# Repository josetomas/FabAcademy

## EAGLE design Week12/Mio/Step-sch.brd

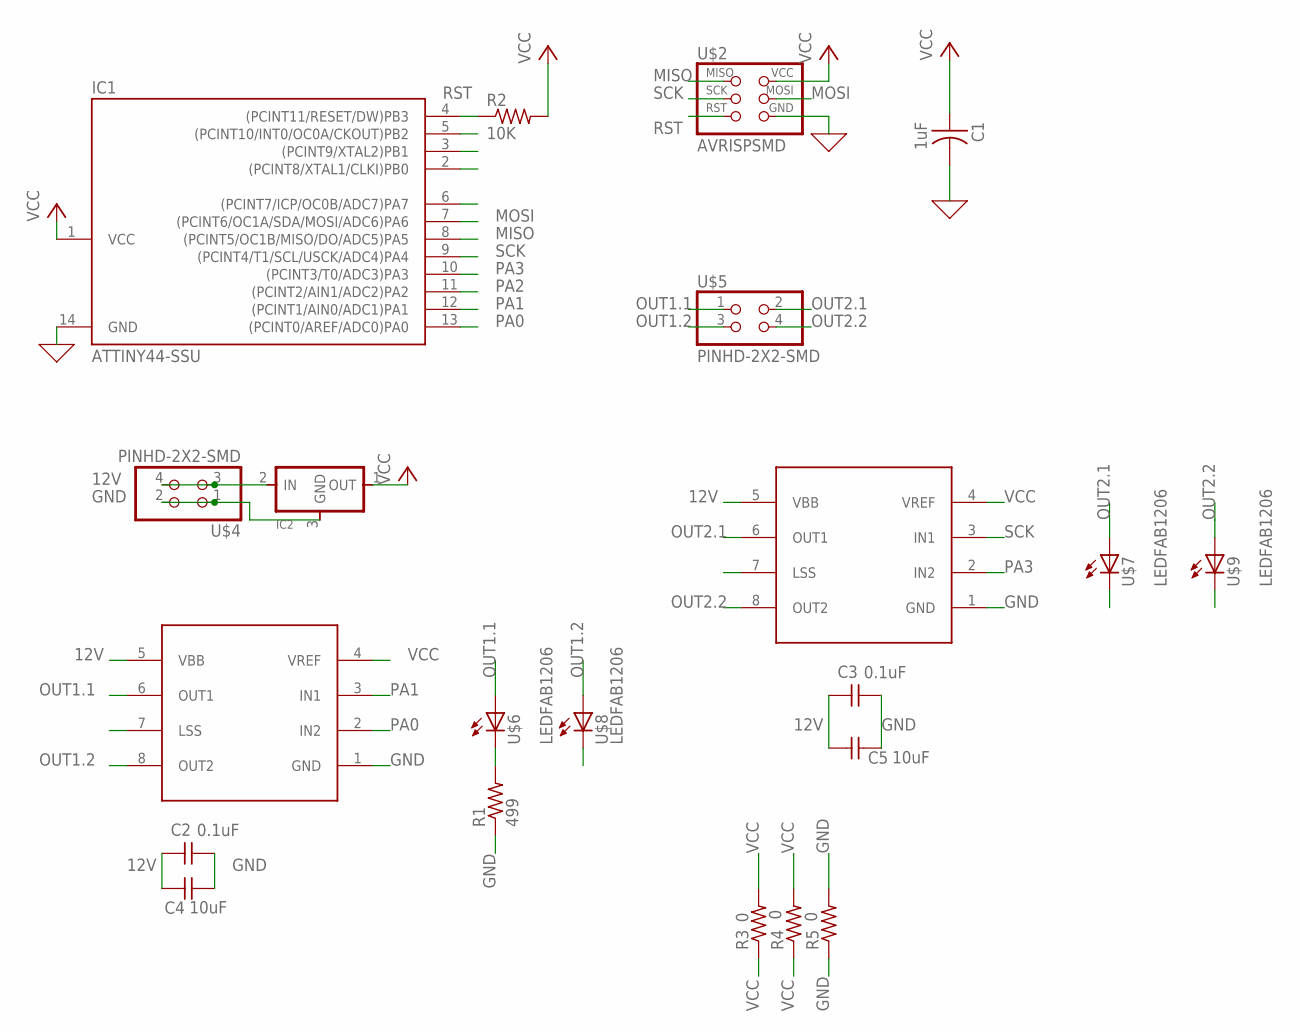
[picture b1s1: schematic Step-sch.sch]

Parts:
C1: 1uF; C1206FAB
C2, C3: 0.1uF; C1206FAB
C4, C5: 10uF; C1206FAB
IC1: ATTINY44-SSU; SOIC14
IC2: REGULATORSOT23; SOT23
R1: 499; R1206FAB
R2: 10K; R1206FAB
R3, R4, R5: 0; R1206FAB
U$1, U$3: A4953-H-BRIDGE-MOTOR-DRIVER; SOIC8
U$2: AVRISPSMD; 2X03SMD
U$4, U$5: PINHD-2X2-SMD; 2X02SMD
U$6, U$7, U$8, U$9: LEDFAB1206; LED1206FAB

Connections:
12V: C2.1, C3.1, C4.1, C5.1, IC2.2 (IN), U$1.5 (VBB), U$3.5 (VBB), U$4.3, U$4.4
GND: C1.2, C2.2, C3.2, C4.2, C5.2, IC1.14 (GND), IC2.3 (GND), R1.1, R5.1, R5.2, U$1.1 (GND), U$2.6 (GND), U$3.1 (GND), U$4.1, U$4.2
MISO: IC1.6 ((PCINT7/ICP/OC0B/ADC7)PA7), IC1.8 ((PCINT5/OC1B/MISO/DO/ADC5)PA5), U$2.1 (MISO)
MOSI: IC1.7 ((PCINT6/OC1A/SDA/MOSI/ADC6)PA6), U$2.4 (MOSI)
OUT1.1: U$1.6 (OUT1), U$5.1, U$6.1 (A)
OUT1.2: U$1.8 (OUT2), U$5.3, U$8.1 (A)
OUT2.1: U$3.6 (OUT1), U$5.2, U$7.1 (A)
OUT2.2: U$3.8 (OUT2), U$5.4, U$9.1 (A)
PA0: IC1.13 ((PCINT0/AREF/ADC0)PA0), U$1.2 (IN2)
PA1: IC1.12 ((PCINT1/AIN0/ADC1)PA1), U$1.3 (IN1)
PA2: IC1.11 ((PCINT2/AIN1/ADC2)PA2)
PA3: IC1.10 ((PCINT3/T0/ADC3)PA3), U$3.2 (IN2)
RES: R1.2, U$6.2 (C), U$7.2 (C), U$8.2 (C), U$9.2 (C)
RST: IC1.4 ((PCINT11/RESET/DW)PB3), R2.1, U$2.5 (RST)
SCK: IC1.9 ((PCINT4/T1/SCL/USCK/ADC4)PA4), U$2.3 (SCK), U$3.3 (IN1)
VCC: C1.1, IC1.1 (VCC), IC2.1 (OUT), R2.2, R3.1, R3.2, R4.1, R4.2, U$1.4 (VREF), U$2.2 (VCC), U$3.4 (VREF)

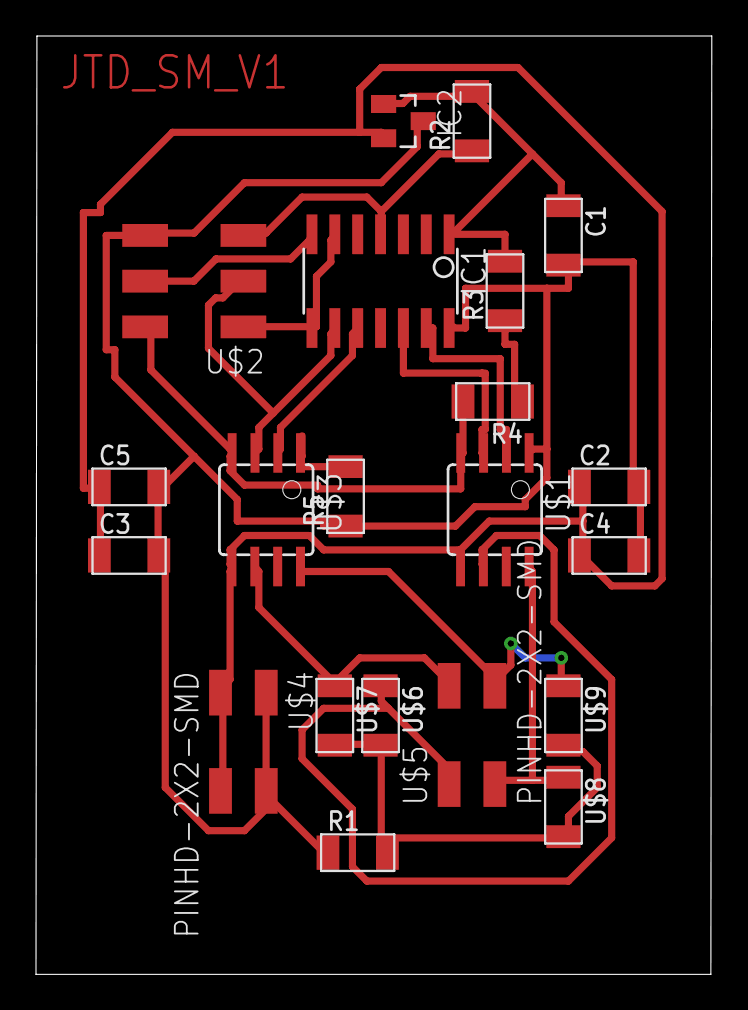
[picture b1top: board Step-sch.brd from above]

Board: 2 copper layers, 37.5 x 52.1 mm, 21 parts (0 on the bottom side), 15 nets.

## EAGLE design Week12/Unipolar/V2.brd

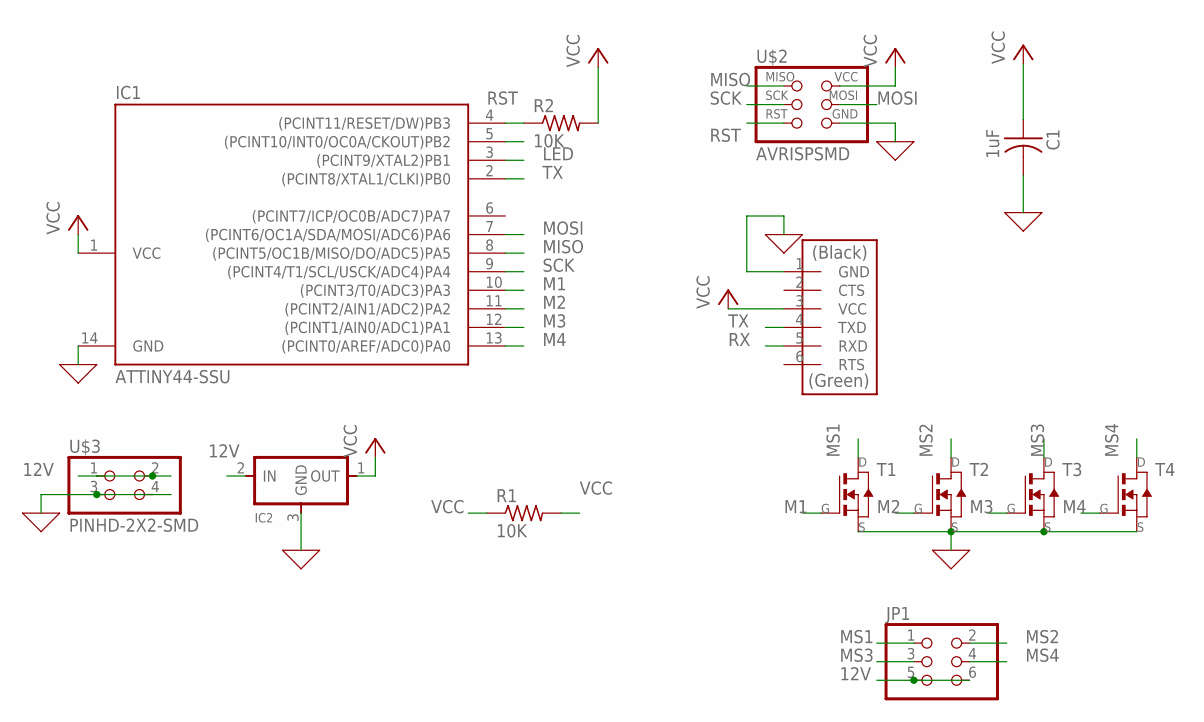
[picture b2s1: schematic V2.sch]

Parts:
C1: 1uF; C1206FAB
IC1: ATTINY44-SSU; SOIC14
IC2: REGULATORSOT23; SOT23
JP1: PINHD-2X3-SMD; 2X03SMD
R1, R2: 10K; R1206FAB
T1, T2, T3, T4: NMOSFETSOT23; SOT-23
U$1: FTDI-SMD-HEADER; 1X06SMD
U$2: AVRISPSMD; 2X03SMD
U$3: PINHD-2X2-SMD; 2X02SMD

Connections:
0: C1.2, IC1.14 (GND), IC2.3 (GND), T1.2 (S), T2.2 (S), T3.2 (S), T4.2 (S), U$1.1 (GND), U$2.6 (GND), U$3.3, U$3.4
12V: IC2.2 (IN), JP1.5, JP1.6, U$3.1, U$3.2
LED: IC1.3 ((PCINT9/XTAL2)PB1)
M1: IC1.10 ((PCINT3/T0/ADC3)PA3), T1.3 (G)
M2: IC1.11 ((PCINT2/AIN1/ADC2)PA2), T2.3 (G)
M3: IC1.12 ((PCINT1/AIN0/ADC1)PA1), T3.3 (G)
M4: IC1.13 ((PCINT0/AREF/ADC0)PA0), T4.3 (G)
MISO: IC1.8 ((PCINT5/OC1B/MISO/DO/ADC5)PA5), U$2.1 (MISO)
MOSI: IC1.7 ((PCINT6/OC1A/SDA/MOSI/ADC6)PA6), U$2.4 (MOSI)
MS1: JP1.1, T1.1 (D)
MS2: JP1.2, T2.1 (D)
MS3: JP1.3, T3.1 (D)
MS4: JP1.4, T4.1 (D)
RST: IC1.4 ((PCINT11/RESET/DW)PB3), R2.1, U$2.5 (RST)
RX: U$1.5 (RXD)
SCK: IC1.9 ((PCINT4/T1/SCL/USCK/ADC4)PA4), U$2.3 (SCK)
TX: IC1.2 ((PCINT8/XTAL1/CLKI)PB0), U$1.4 (TXD)
VCC: C1.1, IC1.1 (VCC), IC2.1 (OUT), R1.1, R1.2, R2.2, U$1.3 (VCC), U$2.2 (VCC)

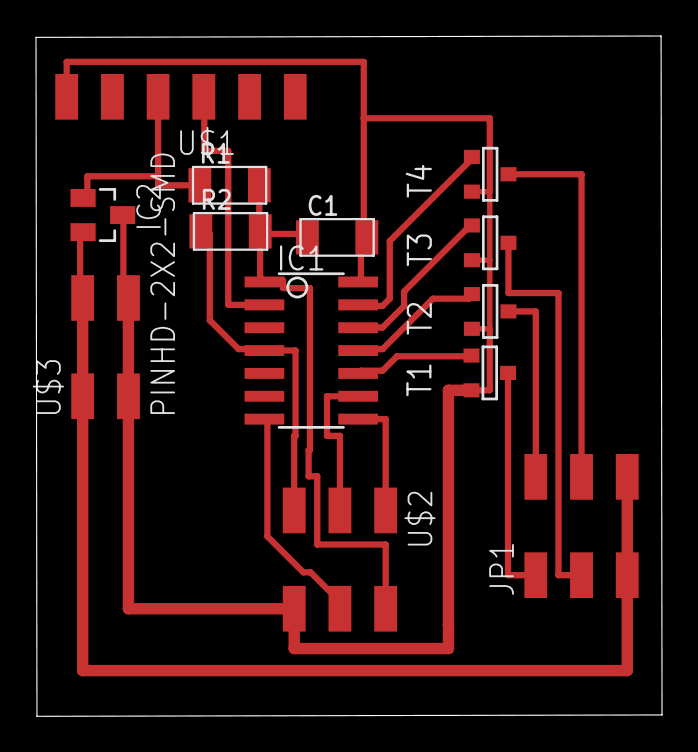
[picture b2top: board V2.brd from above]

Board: 2 copper layers, 34.8 x 37.8 mm, 13 parts (0 on the bottom side), 16 nets.

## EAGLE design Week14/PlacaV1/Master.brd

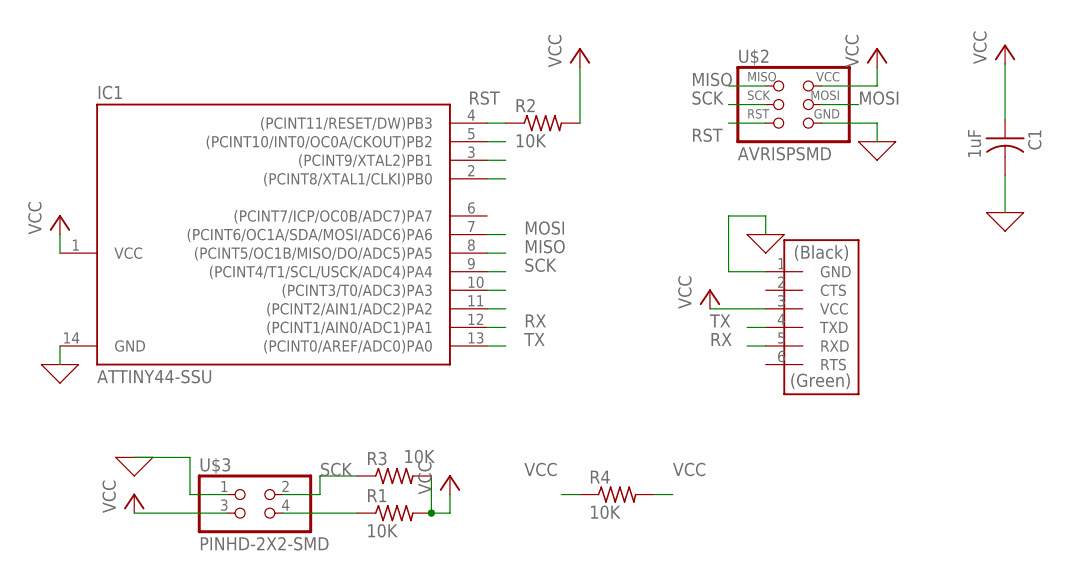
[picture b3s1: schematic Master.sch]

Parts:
C1: 1uF; C1206FAB
IC1: ATTINY44-SSU; SOIC14
R1, R2, R3, R4: 10K; R1206FAB
U$1: FTDI-SMD-HEADER; 1X06SMD
U$2: AVRISPSMD; 2X03SMD
U$3: PINHD-2X2-SMD; 2X02SMD

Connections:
0: C1.2, IC1.14 (GND), U$1.1 (GND), U$2.6 (GND), U$3.1
MISO: IC1.8 ((PCINT5/OC1B/MISO/DO/ADC5)PA5), U$2.1 (MISO)
MOSI: IC1.7 ((PCINT6/OC1A/SDA/MOSI/ADC6)PA6), R1.1, U$2.4 (MOSI), U$3.4
RST: IC1.4 ((PCINT11/RESET/DW)PB3), R2.1, U$2.5 (RST)
RX: IC1.12 ((PCINT1/AIN0/ADC1)PA1), U$1.5 (RXD)
SCK: IC1.9 ((PCINT4/T1/SCL/USCK/ADC4)PA4), R3.1, U$2.3 (SCK), U$3.2
TX: IC1.13 ((PCINT0/AREF/ADC0)PA0), U$1.4 (TXD)
VCC: C1.1, IC1.1 (VCC), R1.2, R2.2, R3.2, R4.1, R4.2, U$1.3 (VCC), U$2.2 (VCC), U$3.3

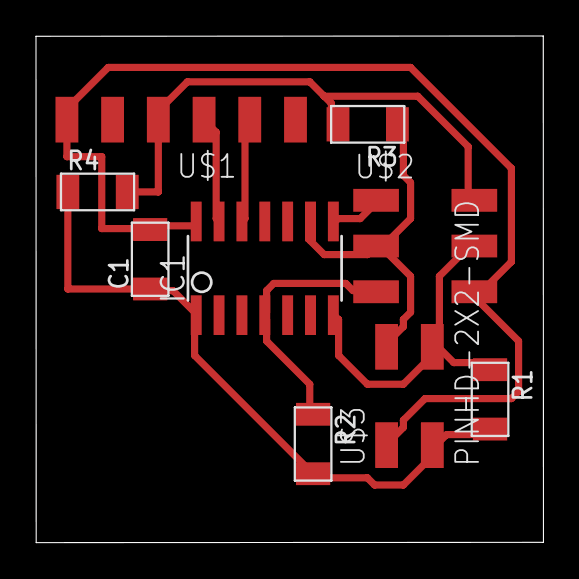
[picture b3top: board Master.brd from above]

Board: 2 copper layers, 28.2 x 28.1 mm, 9 parts (0 on the bottom side), 8 nets.

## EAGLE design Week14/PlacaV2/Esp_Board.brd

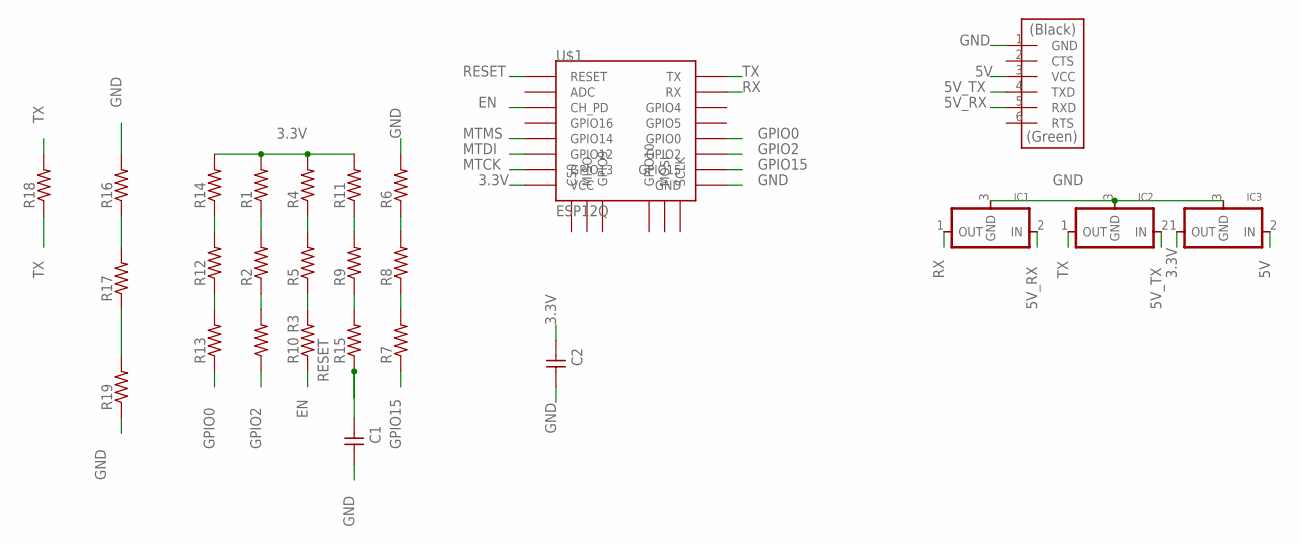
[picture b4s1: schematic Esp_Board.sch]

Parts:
C1, C2: CAP-UNPOLARIZEDFAB; C1206FAB
IC1, IC2, IC3: REGULATORSOT23; SOT23
R1, R2, R3, R4, R5, R6, R7, R8, R9, R10, R11, R12, R13, R14, R15, R16, R17, R18, R19: RES-US1206FAB; R1206FAB
U$1: ESP12Q
U$2: FTDI-SMD-HEADER; 1X06SMD

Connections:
3.3V: C2.1, IC3.1 (OUT), R1.2, R4.2, R11.2, R14.2, U$1.VCC
5V: IC3.2 (IN), U$2.3 (VCC)
5V_RX: IC1.2 (IN), U$2.5 (RXD)
5V_TX: IC2.2 (IN), U$2.4 (TXD)
EN: R10.1, U$1.CH_PD
GND: C1.2, C2.2, IC1.3 (GND), IC2.3 (GND), IC3.3 (GND), R6.2, R16.1, R16.2, R17.1, R17.2, R19.1, R19.2, U$1.GND, U$2.1 (GND)
GPIO0: R13.1, U$1.GPIO0
GPIO2: R3.1, U$1.GPIO2
GPIO15: R7.1, U$1.GPIO15
MTCK: U$1.GPIO13
MTDI: U$1.GPIO12
MTMS: U$1.GPIO14
unnamed: R12.2, R14.1
unnamed: R12.1, R13.2
unnamed: R2.1, R3.2
unnamed: R1.1, R2.2
unnamed: R4.1, R5.2
unnamed: R5.1, R10.2
unnamed: R9.1, R15.2
unnamed: R9.2, R11.1
unnamed: R6.1, R8.2
unnamed: R7.2, R8.1
RESET: C1.1, R15.1, U$1.RESET
RX: IC1.1 (OUT), U$1.RX
TX: IC2.1 (OUT), R18.1, R18.2, U$1.TX

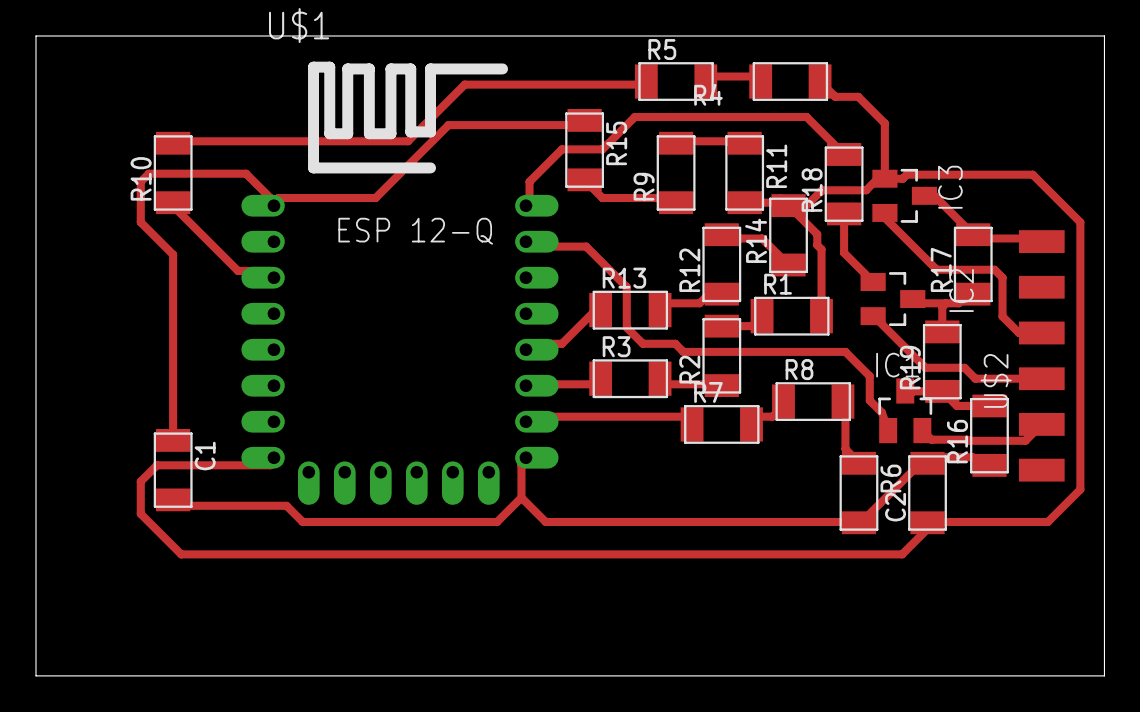
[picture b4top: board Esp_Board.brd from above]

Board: 2 copper layers, 59.4 x 35.5 mm, 26 parts (0 on the bottom side), 22 nets.

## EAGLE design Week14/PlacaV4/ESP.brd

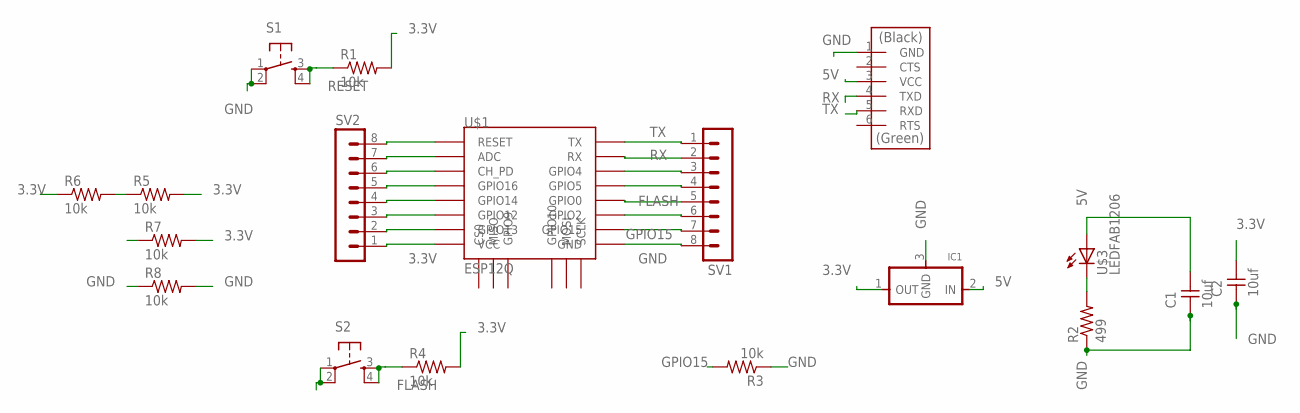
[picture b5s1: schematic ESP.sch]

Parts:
C1, C2: 10uf; C1206FAB
IC1: REGULATORSOT23; SOT23
R1, R3, R4, R5, R6, R7, R8: 10k; R1206FAB
R2: 499; R1206FAB
S1, S2: 6MM_SWITCH6MM_SWITCH; 6MM_SWITCH
SV1, SV2: MA08-1
U$1: ESP12Q
U$2: FTDI-SMD-HEADER; 1X06SMD
U$3: LEDFAB1206; LED1206FAB

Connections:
3.3V: C2.2, IC1.1 (OUT), R1.2, R4.2, R5.1, R5.2, R6.1, R6.2, R7.1, R7.2, SV2.1, U$1.VCC
5V: C1.2, IC1.2 (IN), U$2.3 (VCC), U$3.1 (A)
FLASH: R4.1, S2.3 (S), S2.4 (S1), SV1.5, U$1.GPIO0
GND: C1.1, C2.1, IC1.3 (GND), R2.1, R3.1, R8.1, R8.2, S1.1, S1.2 (P1), SV1.8, U$1.GND, U$2.1 (GND)
GND1: S2.1, S2.2 (P1)
GPIO15: R3.2, SV1.7, U$1.GPIO15
unnamed: SV2.2, U$1.GPIO13
unnamed: SV2.3, U$1.GPIO12
unnamed: SV2.4, U$1.GPIO14
unnamed: SV2.5, U$1.GPIO16
unnamed: SV2.6, U$1.CH_PD
unnamed: SV2.7, U$1.ADC
unnamed: R2.2, U$3.2 (C)
unnamed: SV1.3, U$1.GPIO4
unnamed: SV1.4, U$1.GPIO5
unnamed: SV1.6, U$1.GPIO2
RESET: R1.1, S1.3 (S), S1.4 (S1), SV2.8, U$1.RESET
RX: SV1.2, U$1.RX, U$2.4 (TXD)
TX: SV1.1, U$1.TX, U$2.5 (RXD)

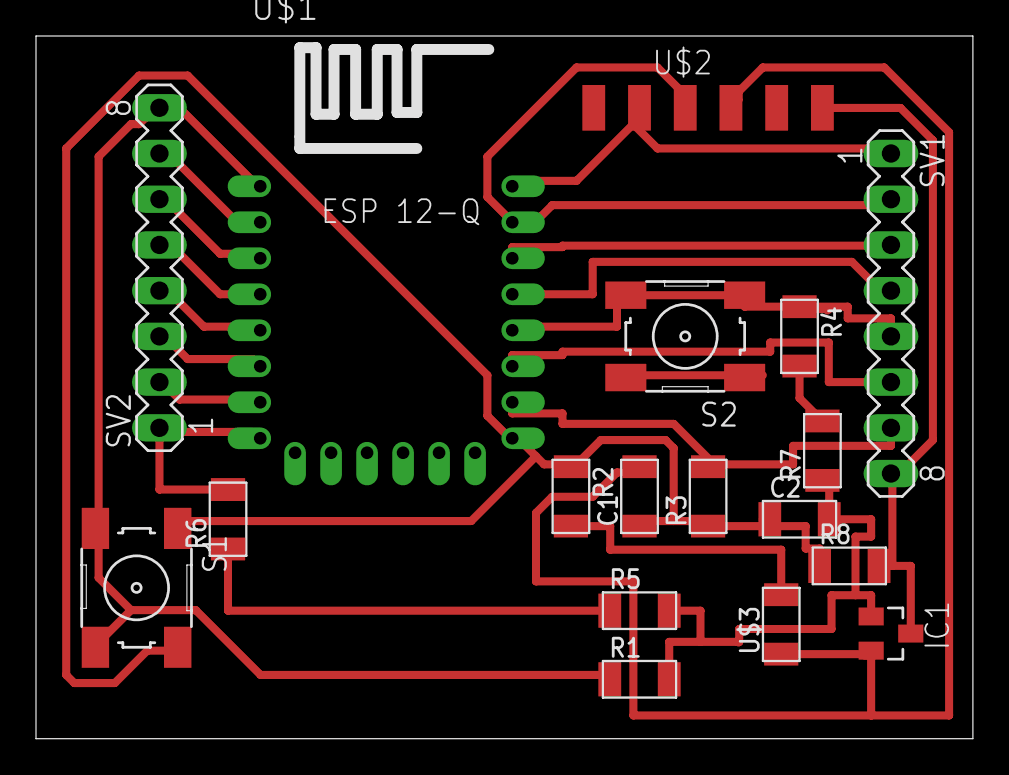
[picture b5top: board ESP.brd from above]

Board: 2 copper layers, 52.0 x 39.0 mm, 18 parts (0 on the bottom side), 19 nets.

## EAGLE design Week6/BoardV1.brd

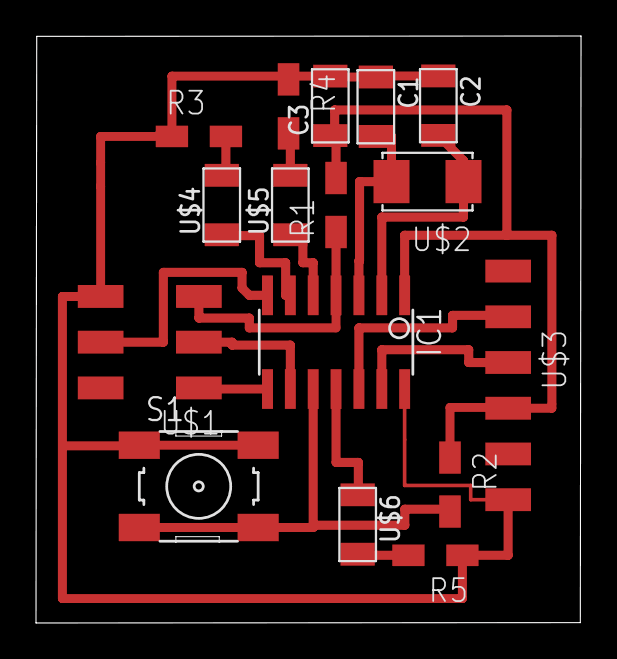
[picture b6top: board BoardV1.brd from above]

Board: 2 copper layers, 30.3 x 32.6 mm, 16 parts (0 on the bottom side), 17 nets.

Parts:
C1, C2: 22pF; C1206FAB
C3: 1uF; C1206FAB
IC1: ATTINY44-SSU; SOIC14
R1, R2, R3, R4, R5: 10K; R1206W
S1: 6MM_SWITCH
U$1: AVRISPSMD; 2X03SMD
U$2: CRYSTAL; 2-SMD-5X3MM
U$3: FTDI-SMD-HEADER; 1X06SMD
U$4, U$5, U$6: LEDFAB1206; LED1206FAB

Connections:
BUTTON: IC1.10, R2.2, S1.3, S1.4
GND: C1.1, C2.1, C3.2, IC1.14, R3.1, R4.1, R5.1, S1.1, S1.2, U$1.6, U$3.1
LED1: IC1.6, U$4.1
LED2: IC1.5, U$5.1
LED3: IC1.11, U$6.1
MISO: IC1.8, U$1.1
MOSI: IC1.7, U$1.4
unnamed: C1.2, IC1.3, U$2.P$2
unnamed: C2.2, IC1.2, U$2.P$1
unnamed: R3.2, U$4.2
unnamed: R4.2, U$5.2
unnamed: R5.2, U$6.2
RST: IC1.4, R1.1, U$1.5
RX: IC1.12, U$3.5
SCK: IC1.9, U$1.3
TX: IC1.13, U$3.4
VCC: C3.1, IC1.1, R1.2, R2.1, U$1.2, U$3.3

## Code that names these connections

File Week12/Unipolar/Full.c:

//
//
// hello.stepper.44.full.c
//
// full stepping hello-world
//
// Neil Gershenfeld
// 11/14/10
//
// (c) Massachusetts Institute of Technology 2010
// This work may be reproduced, modified, distributed,
// performed, and displayed for any purpose. Copyright is
// retained and must be preserved. The work is provided
// as is; no warranty is provided, and users accept all 
// liability.
//

#include <avr/io.h>
#include <util/delay.h>

#define output(directions,pin) (directions |= pin) // set port direction for output
#define set(port,pin) (port |= pin) // set port pin
#define clear(port,pin) (port &= (~pin)) // clear port pin
#define pin_test(pins,pin) (pins & pin) // test for port pin
#define bit_test(byte,bit) (byte & (1 << bit)) // test for bit set

#define MOSFET_port PORTA // MOSFET port
#define MOSFET_direction DDRA // MOSFET direction
#define brown (1 << PA1) // MOSFET output pins
#define black (1 << PA0) // "
#define yellow (1 << PA3) // "
#define orange (1 << PA2) // "
#define on_delay() _delay_us(30) // PWM on time
#define off_delay() _delay_us(2) // PWM off time
#define PWM_count 200 // number of PWM cycles

static uint8_t count;

//
// yellow, brown PWM pulse
//
void pulse_yellow_brown() {
   for (count = 0; count < PWM_count; ++count) {
      set(MOSFET_port, yellow);
      set(MOSFET_port, brown);
      on_delay();
      clear(MOSFET_port, yellow);
      clear(MOSFET_port, brown);
      off_delay();
      }
   }
//
// yellow, black PWM pulse
//
void pulse_yellow_black() {
   for (count = 0; count < PWM_count; ++count) {
      set(MOSFET_port, yellow);
      set(MOSFET_port, black);
      on_delay();
      clear(MOSFET_port, yellow);
      clear(MOSFET_port, black);
      off_delay();
      }
   }
//
// orange, brown PWM pulse
//
void pulse_orange_brown() {
   for (count = 0; count < PWM_count; ++count) {
      set(MOSFET_port, orange);
      set(MOSFET_port, brown);
      on_delay();
      clear(MOSFET_port, orange);
      clear(MOSFET_port, brown);
      off_delay();
      }
   }
//
// orange, black PWM pulse
//
void pulse_orange_black() {
   for (count = 0; count < PWM_count; ++count) {
      set(MOSFET_port, orange);
      set(MOSFET_port, black);
      on_delay();
      clear(MOSFET_port, orange);
      clear(MOSFET_port, black);
      off_delay();
      }
   }
//
// clockwise step
//
void step_cw() {
   pulse_yellow_brown();
   pulse_yellow_black();
   pulse_orange_black();
   pulse_orange_brown();
   }
//
// counter-clockwise step
//
void step_ccw() {
   pulse_orange_brown();
   pulse_orange_black();
   pulse_yellow_black();
   pulse_yellow_brown();
   }

int main(void) {
   //
   // main
   //
   static uint8_t i,j;
   //
   // set clock divider to /1
   //
   CLKPR = (1 << CLKPCE);
   CLKPR = (0 << CLKPS3) | (0 << CLKPS2) | (0 << CLKPS1) | (0 << CLKPS0);
   //
   // initialize MOSFET pins
   //
   clear(MOSFET_port, brown);
   output(MOSFET_direction, brown);
   clear(MOSFET_port, black);
   output(MOSFET_direction, black);
   clear(MOSFET_port, yellow);
   output(MOSFET_direction, yellow);
   clear(MOSFET_port, orange);
   output(MOSFET_direction, orange);
   //
   // main loop
   //
   while (1) {
      for (i = 0; i < 10; ++i) {
         for (j = 0; j < i; ++j)
            step_ccw();
         /*for (j = 0; j < i; ++j)
            step_ccw();*/
         }
      /*for (i = 10; i > 0; --i) {
         for (j = 0; j < i; ++j)
            step_cw();
         for (j = 0; j < i; ++j)
            step_ccw();
         }*/
      }
   }
